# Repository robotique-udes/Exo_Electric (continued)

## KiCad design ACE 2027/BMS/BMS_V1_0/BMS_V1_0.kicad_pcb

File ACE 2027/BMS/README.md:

# BMS — Battery Management System

> Carte de gestion, de protection et de distribution de l'alimentation de l'exosquelette.

Le BMS est responsable de la gestion, de la protection et de la distribution de l'énergie du système. Il supervise les deux batteries, gère les séquences de commutation, protège les circuits contre les défauts et alimente les sous-systèmes critiques, notamment les rails **5 V** et **48 V**.

## Vue d'ensemble

Le BMS doit notamment :

- gérer l'arrêt d'urgence de l'exosquelette ;
- protéger chaque batterie individuellement ;
- sélectionner automatiquement ou manuellement la source d'alimentation active ;
- distribuer les tensions **5 V** et **48 V** aux sous-systèmes ;
- communiquer l'état du système au module principal (**MoBo**) ;
- sécuriser les circuits vis-à-vis des courts-circuits, de la polarité inversée et des surintensités.

## Objectifs fonctionnels

- gérer l'arrêt d'urgence de l'exosquelette ;
- intégrer des fusibles de sécurité : un par batterie, un par jambe et un pour le circuit 5 V ;
- inclure une protection contre la polarité inversée (back-EMF / courant inverse) ;
- mettre en place une stratégie de handshake ou équivalent pour éviter le court-circuit entre les batteries ;
- ajouter des LED indiquant l'état d'alimentation après les fusibles pour vérifier rapidement leur état ;
- gérer un courant continu de **4 A à 48 V** ;
- fournir **2,5 A à 5 V continu** pour les sous-systèmes (BIMU, MoBo et alimentation du BMS) ;
- fournir un indicateur de pourcentage de batterie restante ;
- intégrer une connexion de batterie de type **XT ?** ;
- prévoir une connexion Ethernet pour la distribution 5 V et le bus CAN ;
- intégrer une connexion **XT30** par jambe ;
- permettre le basculement automatique entre les batteries ;
- inclure des indicateurs visuels d'état autour des batteries.

# Conception

- Seuls les ESP32 du **MoBo** et du **BMS** disposent d'une connectivité sans fil. Les deux sont inclus dans le budget de puissance, mais seul le module sans fil du MoBo sera utilisé en fonctionnement normal.
- La consommation **MISC** correspond à une estimation des pertes du PCB, des pertes de conversion, des composants annexes et des LED.
- **LED_BMS** représente la puissance disponible pour des LED décoratives ou d'usage non critique. Elle ne fait pas partie du total de puissance de base et pourra être calculée une fois les besoins principaux fixés.

### Budget de puissance 5 V

Les estimations ci-dessous supposent un rail **3,3 V** et une marge de conversion de **20 %**.

| Charge | Hypothèse | Puissance estimée |
| --- | --- | ---: |
| MoBo | `(300 mA + 100 mA MISC) × 3,3 V` | **1,32 W** |
| BIMU | `(35 mA + 100 mA MISC) × 3,3 V x 5` | **2,25 W** |
| BMS | `(300 mA + 100 mA MISC) × 3,3 V` | **1,32 W** + `LED_BMS` |

Un rendement de **80 %** est retenu pour le convertisseur principal vers **5 V**. Cette hypothèse est volontairement prudente, car la tension de batterie peut varier significativement et le convertisseur doit couvrir une large plage d'entrée.

### Estimation des besoins du circuit 5 V

```text
P nécessaire = (1,32 W + 2,25 W + 1,32 W) / 0,80
            = 6,12 W

I sous 5 V = 6,12 W / 5 V
           = 1,224 A
```

Un convertisseur **5 V / 1.5 A** couvrirait donc l'estimation actuelle. Cependant, le câble Ethernet envisagé, avec des conducteurs **23 AWG**, est généralement estimé à environ **0,7 A par conducteur**. Avec trois conducteurs 5 V et trois conducteurs GND, la capacité théorique atteint :

```text
0,7 A × 3 = 2,1 A
```

Par prudence et pour garder une marge d'évolution, le convertisseur cible sera choisi dans une plage de **2 à 4 A**, selon les besoins confirmés et les composants disponibles. Un fusible de **2 A** en amont du câble est envisagé.

### Estimation des pertes de la diode de contrôle

Le courant traversant la diode est estimé dans le pire cas : **4 A sous 5 V**.

```text
I diode = 4 A × 5 V / 0,8 / 60
        = 0,42 A
```

En appliquant la formule donnée dans la documentation :

```text
P = 0,54 × IF + 0,08 × IF^2
P = 0,54 × 0,42 A + 0,08 × (0,42 A)^2
P = 0,24 W
```

Cette valeur correspond au pire cas et semble acceptable à ce stade. La température de fonctionnement devra toutefois être vérifiée avec le boîtier et le PCB définitifs.

---

## Sécurité et protection des fusibles

### Estimation du courant requis pour le rail 48 V

Le système est composé de :

- 4 moteurs, chacun consommant jusqu'à **0,8 A sous 48 V** ;
- une charge auxiliaire (contrôle) de **1 A sous 5 V**.

#### Courant nominal des moteurs

```text
I moteurs = 4 × 0,8 A
          = 3,2 A
```

#### Courant équivalent de la charge 5 V

En considérant un rendement du convertisseur de **80 %** :

```text
I 5V = (0,8 × 48 V) / (5 V × 1 A)
     = 0,13 A
```

#### Courant total

```text
I total = 3,2 A + 0,13 A
        = 3,33 A
```

#### Marge de sécurité

Avec une marge de sécurité de **25 %** :

```text
I fusible = 3,33 A × 1,25
          ≈ 4,17 A
```

Un fusible de **4 A** serait une valeur limite. Il serait judicieux d'envisager un fusible de **5 A** pour conserver une marge de fonctionnement plus confortable.

### Courant de démarrage

Le fusible doit supporter les pointes de courant produites lors du démarrage des moteurs sans ouvrir prématurément.

Le courant réel pendant le démarrage est :

```text
I start = I normal + I spike
```

Pour un courant de démarrage approximativement constant :

```text
I²t = I start² × t start
```

Une marge de sécurité peut ensuite être appliquée :

```text
I²t requis = I²t × M
```

où **M** représente la marge de sécurité.

### Calcul de la valeur de fusible pour un type slow blow

Pour calculer la valeur de fusible adaptée à une protection de type **slow blow**, il faut utiliser la formule suivante :

```text
I²t = I peak² × t pulse
```

et déterminer la valeur requise pour la fusible en fonction du profil de courant.

Un exemple de référence compatible avec ce type de besoins est disponible ici :

https://www.littelfuse.com/products/fuses-overcurrent-protection/fuses/axial-radial-thru-hole-fuses#Zi1zZXJpZXM9MzcyJm5mLW1heGltdW1fYWNfdm9sdGFnZV92X2RlY2ltYWw9NzAuLi4xMDAwJm5mLW5vbWluYWxfbWVsdGluZ19pX3NxdWFyZWRfdF9hX3NxdWFyZWRfcGVyX3NlY29uZF9kZWNpbWFsPTE2Li4uMzImY3E9KCU0MGxldmVsdGhyZWVjYXRlZ29yeSUzRCUzRCUyMkF4aWFsJTIwUmFkaWFsJTIwVGhydSUyMEhvbGUlMjBGdXNlcyUyMiklMjAoJTQwbGV2ZWxudW1iZXIlM0QlM0Q3KSUyMCglNDBsZXZlbHR3b2NhdGVnb3J5JTNEJTNEJTIyRnVzZXMlMjIpJTIwKCU0MGxldmVsb25lY2F0ZWdvcnklM0QlM0QlMjJGdXNlcyUyMCUyNiUyME92ZXJjdXJyZW50JTIwUHJvdGVjdGlvbiUyMik=

Mini fuse verre
https://www.digikey.ca/en/products/detail/littelfuse-inc/0225002-MXP/777781

https://www.digikey.ca/en/products/filter/fuses/139?s=N4IgjCBcoGwJxVAYygMwIYBsDOBTANCAPZQDaIAzHAKw0UgC6hADgC5QgDKrATgJYA7AOYgAvoTBwAHAmggUkDDgLEyIAAyNxIAExgALPsQg2HAKoC%2BrAPKoAsrnTYArj1whCzjgDUPIALaCHPpSfv7oAB4cBpraALQ6xgq8ziokkOTUWtqJGSCoznhaQA

## Choix mosfet
La priorité est de minimisé le RDS on pour limité les pertes durant l'utilisation. Il faut aussi gardé 20V de marge sur l'utilisation. Pour finir il faut gardé un Gate charge raisonnable pour limité le temps de transition des mosfet:

Premier choix 80V(31mO, 45nC)
https://www.digikey.ca/en/products/detail/vishay-siliconix/SQS181ELNW-T1-GE3/20512189

Deuxième choix 80V(17mO, 93nC)
https://www.digikey.ca/en/products/detail/mcc-micro-commercial-components/MCAC017P08Y-TP/25965041

Premier choix 100V(30mO, 68nC)
https://www.digikey.ca/en/products/detail/vishay-siliconix/SQJ211ELP-T1-GE3/13540573

Deuxième choix 100V(31mO, 73nC)
https://www.digikey.ca/en/products/detail/goford-semiconductor/GT250P10T/19524544

## calcul led 

Consommation maximum de 11W/m pour les bandes LEDS https://www.amazon.ca/BTF-LIGHTING-Similar-Individually-Addressable-Lighting/dp/B0F62XVXNS/ref=ast_sto_dp_puis?th=1
Donc on parle de 1.1W/m ou 0.22A

Mais une consommation normal serait plus 30% à 40% voir moins(le but est de les voir, mais sans plus), donc on parle de 0.44W/m ou 0.088A. 
---

## Points à confirmer avant validation finale

- référence exacte des batteries, tension minimale et tension maximale ;
- type de connecteur batterie (**XT ?**) et courant admissible réel ;
- courant de démarrage et courant continu de chaque jambe ;
- méthode de mesure de l'état de charge et précision attendue ;   comptage de columbs
- protocole de handshake pour la sélection de batterie et comportement en cas de défaut ;  Utilisation de 3 lectures de tensions
- validation thermique du convertisseur 5 V, des MOSFET et des fusibles ;  Probablement Négligeable

Faire circuit led pour support batterie

## Résumé

Le BMS est un élément central du système d'alimentation. Il doit offrir une protection robuste, une gestion fiable de la source d'énergie, un basculement entre batteries sans court-circuit, ainsi qu'une alimentation stable de la logique de contrôle et des sous-systèmes. Les estimations actuelles indiquent que le rail 5 V doit être dimensionné pour un convertisseur de l'ordre de **2 à 4 A**, tandis que la protection du rail 48 V doit être étudiée avec une marge suffisante pour supporter les pointes de démarrage des moteurs.

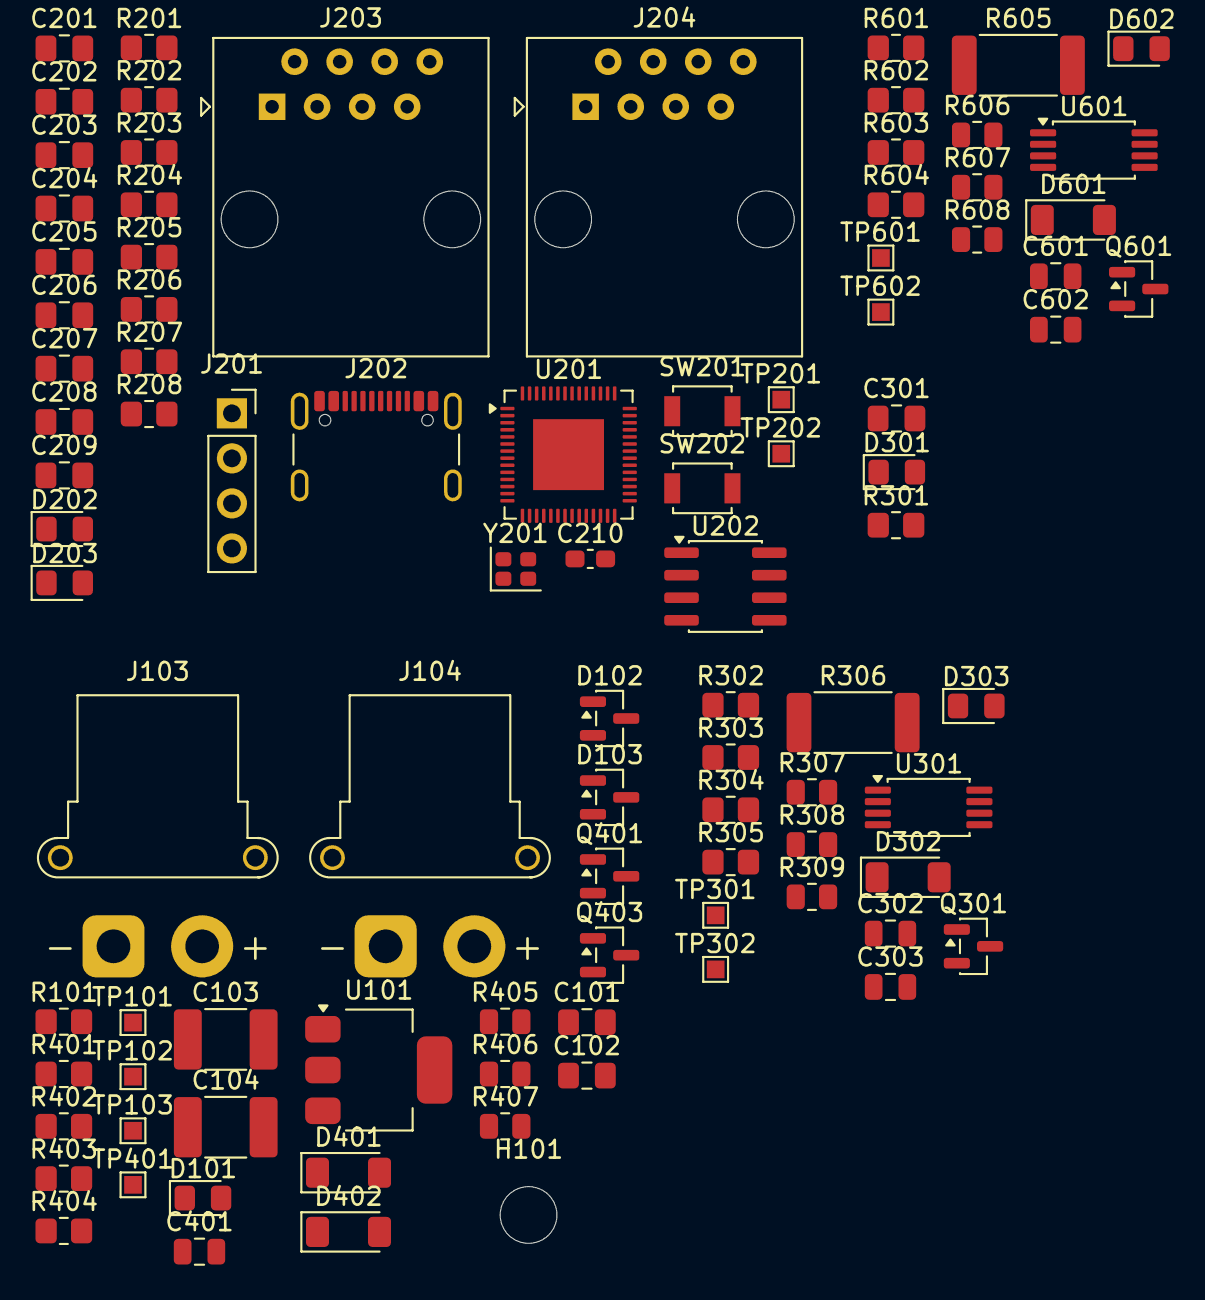
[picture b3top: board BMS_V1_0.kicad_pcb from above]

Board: 4 copper layers, 94 parts (0 on the bottom side), 41 nets, no tracks yet.

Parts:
C101, C102, C301: 4,7µF; C_0805_2012Metric_Pad1.18x1.45mm_HandSolder
C103, C104: 1nF; C_1812_4532Metric_Pad1.57x3.40mm_HandSolder
C201, C209: 22μF; C_0805_2012Metric_Pad1.18x1.45mm_HandSolder
C202, C203, C204, C205, C208: 0.1μF; C_0805_2012Metric_Pad1.18x1.45mm_HandSolder
C206, C207: 12pF; C_0805_2012Metric_Pad1.18x1.45mm_HandSolder
C210: 47nF; C_0603_1608Metric_Pad1.08x0.95mm_HandSolder
C302, C601: 0,1µF; C_0805_2012Metric
C303, C401, C602: 0.1uF; C_0805_2012Metric
D101, D301, D303, D602: POWER LED; LED_0805_2012Metric_Pad1.15x1.40mm_HandSolder
D102, D103: BAV99; SOT-23
D202: CONNECTED LED; LED_0805_2012Metric_Pad1.15x1.40mm_HandSolder
D203: ERROR LED; LED_0805_2012Metric_Pad1.15x1.40mm_HandSolder
D302, D401, D402, D601: BZV55B15; D_MiniMELF
H101: MountingHole; MountingHole_3.2mm_M3_ISO14580
J103: Jambe_gauche; AMASS_XT30PW-F_1x02_P2.50mm_Horizontal
J104: Jambe_droite; AMASS_XT30PW-F_1x02_P2.50mm_Horizontal
J201: UART_connector; PinSocket_1x04_P2.54mm_Vertical
J202: USB_C_Receptacle_USB2.0_16P; USB_C_Receptacle_GCT_USB4105-xx-A_16P_TopMnt_Horizontal
J203: MoBo; RJ45_Amphenol_54602-x08_Horizontal
J204: BIMU; RJ45_Amphenol_54602-x08_Horizontal
Q301, Q401, Q403, Q601: NTR2101P; SOT-23
R101, R205, R206, R301: 330Ω; R_0805_2012Metric_Pad1.20x1.40mm_HandSolder
R201, R202, R203, R204: 5.1KΩ; R_0805_2012Metric_Pad1.20x1.40mm_HandSolder
R207, R208: 50Ω; R_0805_2012Metric_Pad1.20x1.40mm_HandSolder
R302, R303, R304, R305, R401, R402, R403, R404, R601, R602, R603, R604: ???Ω; R_0805_2012Metric_Pad1.20x1.40mm_HandSolder
R306, R605: ???Ω; R_2512_6332Metric_Pad1.40x3.35mm_HandSolder
R307, R405, R606: ???; R_0805_2012Metric
R308, R406, R607: ???Ω; R_0805_2012Metric
R309, R407, R608: 100Ω; R_0805_2012Metric
SW201, SW202: SW_Push; SW_SPST_B3U-1000P
TP101: TP_GND_IN; TestPoint_Pad_1.0x1.0mm
TP102: TP_5V; TestPoint_Pad_1.0x1.0mm
TP103: TP_3v3; TestPoint_Pad_1.0x1.0mm
TP201: TP_CAN_P; TestPoint_Pad_1.0x1.0mm
TP202: TP_CAN_N; TestPoint_Pad_1.0x1.0mm
TP301, TP601: TP_Current; TestPoint_Pad_1.0x1.0mm
TP302, TP401, TP602: TP_Voltage; TestPoint_Pad_1.0x1.0mm
U101: AP7361C-33E; SOT-223-3_TabPin2
U201: ESP32-S3; QFN-56-1EP_7x7mm_P0.4mm_EP4x4mm
U202: SN65HVD232DR; SOIC-8_3.9x4.9mm_P1.27mm
U301, U601: INA240A2PW; TSSOP-8_4.4x3mm_P0.65mm
Y201: ABM8-40.000MHZ-10-D1G-T; Crystal_SMD_2016-4Pin_2.0x1.6mm

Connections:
+3.3V: C102.2, C103.1, C104.1, C201.1, C202.1, C208.1, C209.1, C302.1, C601.1, D102.2 (A), D103.2 (A), R101.1, R203.2, R204.2, TP103.1 (1_1), U101.3 (VO), U201.2 (VDD3P3), U201.3 (VDD3P3), U202.3 (VCC), U301.5 (V+), U301.6 (REF2), U601.5 (V+), U601.6 (REF2)
+5V: C101.2, C203.1, J201.4, J202.A4 (VBUS), J202.A9 (VBUS), J202.B4 (VBUS), J202.B9 (VBUS), J203.5, J203.6, J203.7, J204.7, TP102.1 (1_1), U101.1 (VI)
/Alimentation/Battery_Out_Droite: Q403.2 (S), R403.2, R605.2, R606.2, U601.3 (-)
/Alimentation/Battery_Out_Gauche: Q401.2 (S), R306.2, R307.2, R401.2, U301.3 (-)
/Alimentation/Battery_Sub_Circuit_Droite/Battery_P: Q601.2 (S), R601.2
/Alimentation/Battery_Sub_Circuit_Gauche/Battery_P: Q301.2 (S), R302.2
BOOT: C205.1, R203.1, SW202.2
CAN_N: D103.3 (K), J203.2, J204.2, R208.2, TP202.1 (1_1), U202.6 (CANL)
CAN_P: D102.3 (K), J203.1, J204.1, R207.1, TP201.1 (1_1), U202.7 (CANH)
Current_Sense_Droite: TP601.1 (1_1), U601.8
Current_Sense_Gauche: TP301.1 (1_1), U301.8
EN: C204.1, R204.1, SW201.2
GND: C101.1, C102.1, C103.2, C104.2, C201.2, C202.2, C203.2, C204.2, C205.2, C206.2, C207.2, C208.2, C209.2, C210.1, C302.2, C303.2, C401.2, C601.2, C602.2, D101.1 (K), D102.1 (K), D103.1 (K), D202.1 (K), D203.1 (K), D303.1 (K), D602.1 (K), J103.1, J104.1, J201.1, J202.A1 (GND), J202.A12 (GND), J202.B1 (GND), J202.B12 (GND), J203.3, J203.4, J203.8, J204.8, R201.2, R202.2, R303.1, R308.1, R402.1, R404.1, R406.1, R602.1, R607.1, SW201.1, SW202.1, TP101.1 (1_1), U101.2 (GND), U201.57 (GND), U202.2 (GND), U301.1 (GND), U301.4 (GND), U301.7 (REF1), U601.1 (GND), U601.4 (GND), U601.7 (REF1), Y201.2, Y201.4
unnamed: C210.2, R207.2, R208.1
unnamed: D101.2 (A), R101.2
unnamed: J202.A7 (D-), J202.B7 (D-)
unnamed: J202.A6 (D+), J202.B6 (D+)
unnamed: D202.2 (A), R205.1
unnamed: D203.2 (A), R206.1
unnamed: D302.2 (A), Q301.1 (G), R302.1
unnamed: D303.2 (A), R307.1, R308.2, R309.2
unnamed: D401.2 (A), Q401.1 (G), R401.1
unnamed: D402.2 (A), Q403.1 (G), R403.1
unnamed: D601.2 (A), Q601.1 (G), R601.1
unnamed: D602.2 (A), R606.1, R607.2, R608.2
unnamed: J202.A5 (CC1), R201.1
unnamed: J202.B5 (CC2), R202.1
unnamed: Q301.3 (D), R305.2, R306.1, U301.2 (+)
unnamed: R303.2, R304.2
unnamed: Q601.3 (D), R604.2, R605.1, U601.2 (+)
unnamed: R602.2, R603.2
unnamed: R405.1, R406.2, R407.2
unnamed: U201.55 (VDDA), U201.56 (VDDA)
Sortie_Selecteur: Q401.3 (D), Q403.3 (D), R405.2
U0RX: J201.2, U201.50 (U0RXD)
U0TX: J201.3, U201.49 (U0TXD)
Voltage_Sense_Droite: C602.1, R608.1, TP602.1 (1_1)
Voltage_Sense_Gauche: C303.1, R309.1, TP302.1 (1_1)
Voltage_Sense_Selecteur: C401.1, R407.1, TP401.1 (1_1)
XTAL_N: C207.1, U201.53 (XTAL_N), Y201.3
XTAL_P: C206.1, U201.54 (XTAL_P), Y201.1

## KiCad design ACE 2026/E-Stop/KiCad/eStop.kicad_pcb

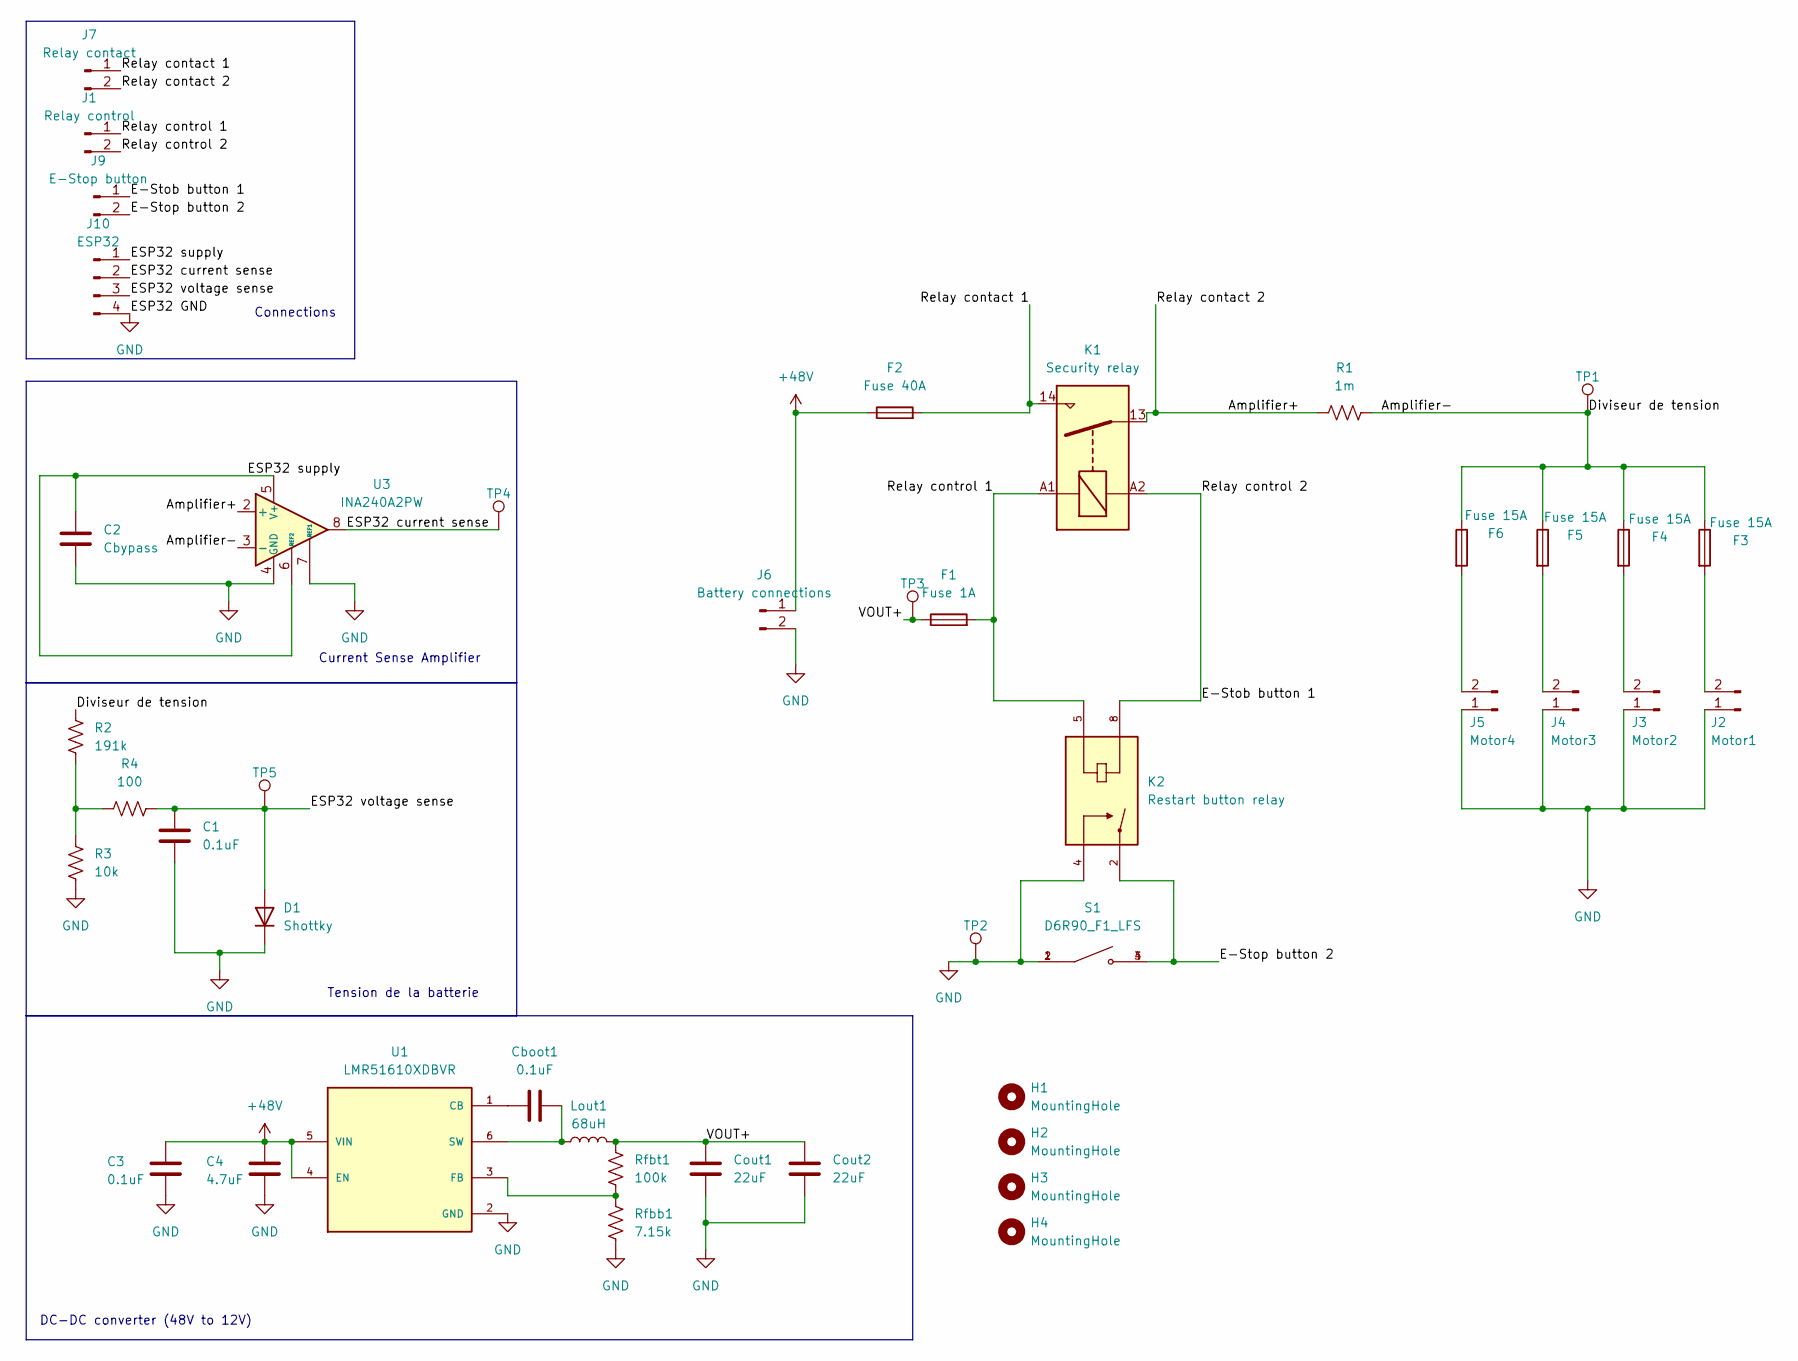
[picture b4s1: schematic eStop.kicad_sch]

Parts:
C1: 0.1uF; C_0805_2012Metric
C2: Cbypass; C_0805_2012Metric
C3: 0.1uF; C_1210_3225Metric_Pad1.33x2.70mm_HandSolder
C4: 4.7uF; C_2220_5750Metric_Pad1.97x5.40mm_HandSolder
Cboot1: 0.1uF; C_0805_2012Metric
Cout1, Cout2: 22uF; C_1210_3225Metric_Pad1.33x2.70mm_HandSolder
D1: Shottky; D_0603_1608Metric_Pad1.05x0.95mm_HandSolder
F1: Fuse 1A; 3557-15_KEY
F2: Fuse 40A; 40A fuse holder
F3, F4, F5, F6: Fuse 15A; 40A fuse holder
H1, H2, H3, H4: MountingHole; MountingHole_3.2mm_M3_DIN965
J1: Relay control; JST_EH_B2B-EH-A_1x02_P2.50mm_Vertical
J2: Motor1; AMASS_XT30U-F_1x02_P5.0mm_Vertical
J3: Motor2; AMASS_XT30U-F_1x02_P5.0mm_Vertical
J4: Motor3; AMASS_XT30U-F_1x02_P5.0mm_Vertical
J5: Motor4; AMASS_XT30U-F_1x02_P5.0mm_Vertical
J6: Battery connections; AMASS_XT60-M_1x02_P7.20mm_Vertical
J7: Relay contact; AMASS_XT60-M_1x02_P7.20mm_Vertical
J9: E-Stop button; JST_EH_B2B-EH-A_1x02_P2.50mm_Vertical
J10: ESP32; JST_EH_B4B-EH-A_1x04_P2.50mm_Vertical
K1: Security relay
K2: Restart button relay; RELAY_G6L-1P_DC12; Digi-Key_PN Z1229-ND
Lout1: 68uH; L_Bourns_SRR1260
R1: 1m; R_2512_6332Metric_Pad1.40x3.35mm_HandSolder
R2: 191k; R_0805_2012Metric
R3: 10k; R_0805_2012Metric
R4: 100; R_0805_2012Metric
Rfbb1: 7.15k; R_0805_2012Metric
Rfbt1: 100k; R_0805_2012Metric
S1: D6R90_F1_LFS; SW_D6R90_F1_LFS; PARTREV N/A
TP1, TP2, TP3, TP4, TP5: 1.0mm; TestPoint_Pad_D4.0mm
U1: LMR51610XDBVR; SOT95P280X145-6N; PARTREV B; DigiKey_Part_Number 296-LMR51610XDBVRCT-ND
U3: INA240A2PW; TSSOP-8_4.4x3mm_P0.65mm

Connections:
+48V: C3.1, C4.1, F2.1, J6.1, U1.4 (EN), U1.5 (VIN)
/Amplifier+: J7.2, K1.13, R1.1, U3.2 (+)
/Amplifier-: F3.1, F4.1, F5.1, F6.1, R1.2, R2.2, TP1.1, U3.3 (-)
/E-Stob button 1: J1.2, J9.1, K1.A2, K2.8; also elsewhere on the board
/E-Stop button 2: J9.2, K2.2, S1.3, S1.4; also elsewhere on the board
/ESP32 current sense: J10.2, TP4.1, U3.8; also elsewhere on the board
/ESP32 supply: C2.1, J10.1, U3.5 (V+), U3.6 (REF2); also elsewhere on the board
/ESP32 voltage sense: C1.1, D1.2 (A), J10.3, R4.1, TP5.1; also elsewhere on the board
/Relay contact 1: F2.2, J7.1, K1.14
/Relay control 1: F1.3, J1.1, K1.A1, K2.5; also elsewhere on the board
/VOUT+: Cout1.2, Cout2.2, F1.1, Lout1.2, Rfbt1.2, TP3.1
GND: C1.2, C2.2, C3.2, C4.2, Cout1.1, Cout2.1, D1.1 (K), J2.1, J3.1, J4.1, J5.1, J6.2, J10.4, K2.4, R3.1, Rfbb1.1, S1.1, S1.2, TP2.1, U1.2 (GND), U3.1 (GND), U3.4 (GND), U3.7 (REF1); also elsewhere on the board
unnamed: F3.2, J2.2
unnamed: F4.2, J3.2
unnamed: F5.2, J4.2
unnamed: F6.2, J5.2
unnamed: R2.1, R3.2, R4.2
unnamed: Cboot1.1, U1.1 (CB)
unnamed: Rfbb1.2, Rfbt1.1, U1.3 (FB)
unnamed: Cboot1.2, Lout1.1, U1.6 (SW)

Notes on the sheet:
Current Sense Amplifier
DC-DC converter (48V to 12V)
Tension de la batterie
Connections

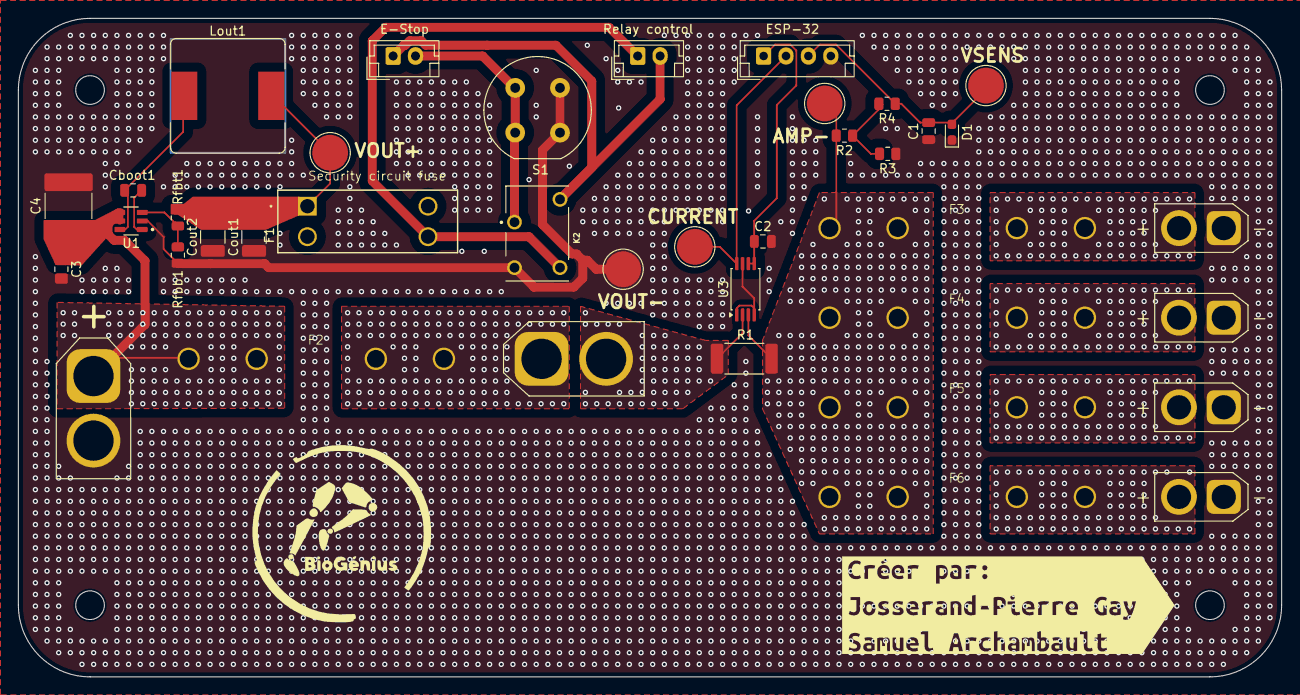
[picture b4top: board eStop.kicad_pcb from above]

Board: 2 copper layers, 141.0 x 73.5 mm, 44 parts (0 on the bottom side), 20 nets.

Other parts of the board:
E-Stop: E-Stop button; JST_EH_B2B-EH-A_1x02_P2.50mm_Vertical
ESP-32 : ESP32; JST_EH_B4B-EH-A_1x04_P2.50mm_Vertical
Relay control: Relay control; JST_EH_B2B-EH-A_1x02_P2.50mm_Vertical
kibuzzard-69BC9173: G***; kibuzzard-69BC9173

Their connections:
/E-Stob button 1: E-Stop.1, Relay control.2; also elsewhere on the board
/E-Stop button 2: E-Stop.2; also elsewhere on the board
/ESP32 current sense: ESP-32.2; also elsewhere on the board
/ESP32 supply: ESP-32.1; also elsewhere on the board
/ESP32 voltage sense: ESP-32.3; also elsewhere on the board
/Relay control 1: Relay control.1; also elsewhere on the board
GND: ESP-32.4; also elsewhere on the board

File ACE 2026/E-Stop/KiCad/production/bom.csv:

Designator,Footprint,Quantity,Value,LCSC Part #
"C1, C3, CBOOT1",0805,3,0.1uF,
C2,0805,1,Cbypass,
C4,2220,1,4.7uF,
"COUT1, COUT2",1210,2,22uF,
D1,0603,1,Shottky,
E-STOP,JST_EH_B2B-EH-A_1x02_P2.50mm_Vertical,1,E-Stop button,
ESP-32 ,JST_EH_B4B-EH-A_1x04_P2.50mm_Vertical,1,ESP32,
F1,3557-15_KEY,1,Fuse 1A,
F2,40A fuse holder,1,Fuse 40A,
"F3, F4, F5, F6",40A fuse holder,4,Fuse 15A,
J2,AMASS_XT30U-F_1x02_P5.0mm_Vertical,1,Motor1,
J3,AMASS_XT30U-F_1x02_P5.0mm_Vertical,1,Motor2,
J4,AMASS_XT30U-F_1x02_P5.0mm_Vertical,1,Motor3,
J5,AMASS_XT30U-F_1x02_P5.0mm_Vertical,1,Motor4,
J6,AMASS_XT60-M_1x02_P7.20mm_Vertical,1,Battery connections,
J7,AMASS_XT60-M_1x02_P7.20mm_Vertical,1,Relay contact,
K2,RELAY_G6L-1P_DC12,1,Restart button relay,
LOUT1,L_Bourns_SRR1260,1,68uH,
R1,2512,1,1m,
R2,0805,1,191k,
R3,0805,1,10k,
R4,0805,1,100,
RELAY CONTROL,JST_EH_B2B-EH-A_1x02_P2.50mm_Vertical,1,Relay control,
RFBB1,0805,1,7.15k,
RFBT1,0805,1,100k,
S1,SW_D6R90_F1_LFS,1,D6R90_F1_LFS,
"TP1, TP2, TP3, TP4, TP5",TestPoint_Pad_D4.0mm,5,1.0mm,
U1,SOT95P280X145-6N,1,LMR51610XDBVR,
U3,TSSOP-8_4.4x3mm_P0.65mm,1,INA240A2PW,

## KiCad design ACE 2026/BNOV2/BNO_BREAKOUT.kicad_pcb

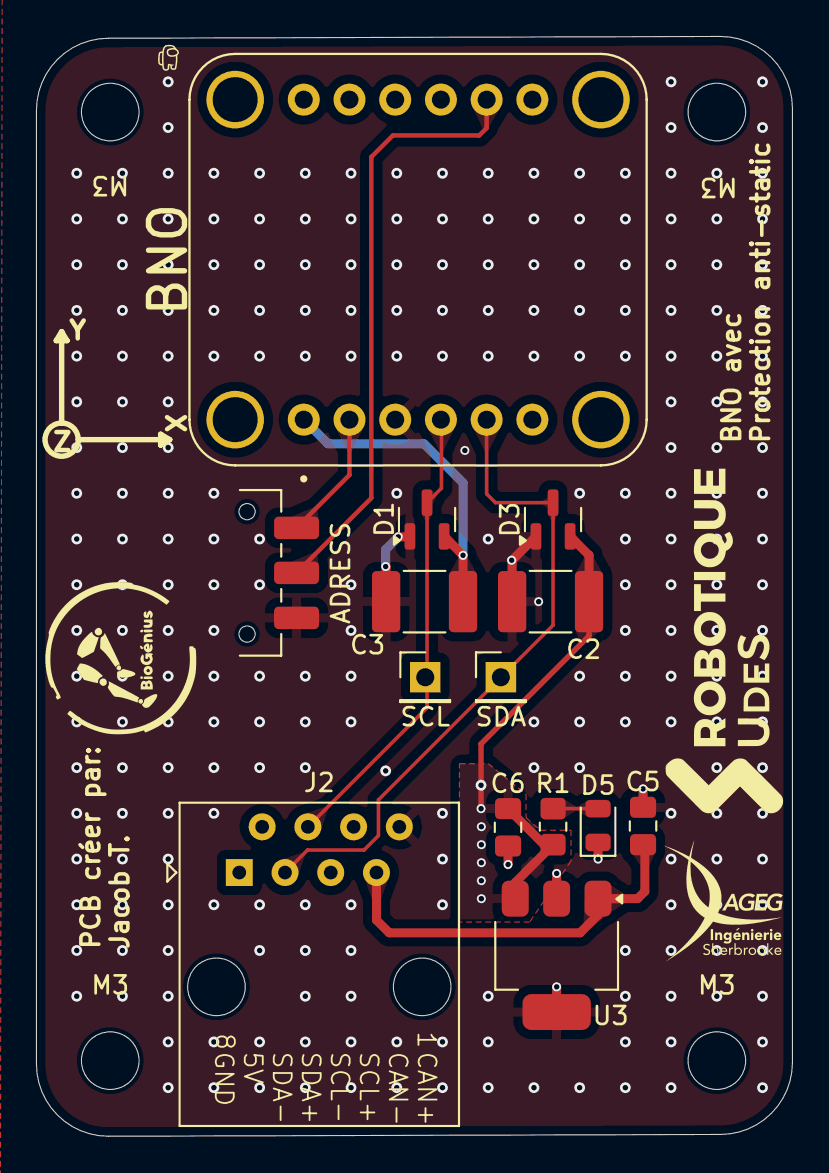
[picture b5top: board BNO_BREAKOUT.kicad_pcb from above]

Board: 2 copper layers, 42.0 x 61.1 mm, 16 parts (0 on the bottom side), 8 nets.

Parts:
ADRESS: SW_SPDT; SW_SPDT_CK_JS102011SAQN
BNO: 4754; MODULE_4754
C2, C3: 1n; C_1812_4532Metric_Pad1.57x3.40mm_HandSolder
C5, C6: 4,7µF; C_0805_2012Metric_Pad1.18x1.45mm_HandSolder
D1, D3: BAV99; SOT-23
D5: Green_power; D_0805_2012Metric
J2: RJ45; RJ45_Amphenol_54602-x08_Horizontal
M3, M3#2: MountingHole_3.2mm_M3
R1: 330; R_0805_2012Metric_Pad1.20x1.40mm_HandSolder
SCL: SCL; PinHeader_1x01_P2.54mm_Vertical
SDA: SDA; PinHeader_1x01_P2.54mm_Vertical
U3: AP7361C-33E; SOT-223-3_TabPin2

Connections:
/3V3: BNO.JP1_1 (VIN), C2.1, C3.1, C6.2, D1.2 (A), D3.2 (A), R1.1, U3.3 (VO)
/5V: C5.2, J2.7, U3.1 (VI)
/SCL: BNO.JP1_4 (SCL), D1.3 (K), J2.4, SCL.1
/SDA: BNO.JP1_5 (SDA), D3.3 (K), J2.3, SDA.1
GND: ADRESS.3 (C), BNO.JP1_3 (GND), C2.2, C3.2, C5.1, C6.1, D1.1 (K), D3.1 (K), D5.1 (K), J2.8, U3.2 (GND)
unnamed: D5.2 (A), R1.2
unnamed: ADRESS.1 (A), BNO.JP1_2 (3VO)
unnamed: ADRESS.2 (B), BNO.JP2_5 (DI)

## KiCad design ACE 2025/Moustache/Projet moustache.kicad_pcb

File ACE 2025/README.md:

# 2025 Standard électronique
Pour la fixation des pcb, il est standardisé d'utiliser des vis M3.
Ne pas utiliser de micro vias.
## PIN Layout pour la communication en cable ethernet
Pin 1: CAN+
Pin 2: CAN-
Pin 3: SCL+
Pin 4: SCL-
Pin 5: SDA+
Pin 6: SDA-
Pin 7: 5V
Pin 8: GND

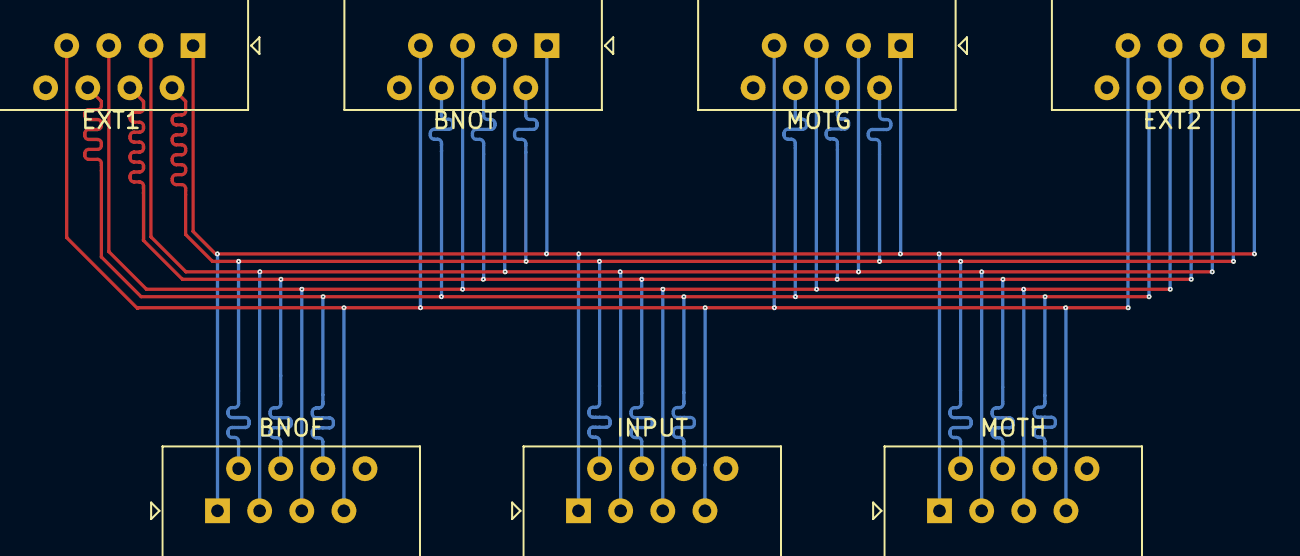
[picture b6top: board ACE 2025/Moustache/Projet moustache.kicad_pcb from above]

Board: 2 copper layers, 9 parts (0 on the bottom side), 8 nets.

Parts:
BNOF: RJ45; RJ45_Amphenol_54602-x08_Horizontal
BNOT: RJ45; RJ45_Amphenol_54602-x08_Horizontal
EXT1, EXT2: RJ45; RJ45_Amphenol_54602-x08_Horizontal
H1, H2: MountingHole; MountingHole_3.2mm_M3
INPUT: RJ45; RJ45_Amphenol_54602-x08_Horizontal
MOTG: RJ45; RJ45_Amphenol_54602-x08_Horizontal
MOTH: RJ45; RJ45_Amphenol_54602-x08_Horizontal

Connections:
+5V: BNOF.7, BNOT.7, EXT1.7, EXT2.7, INPUT.7, MOTG.7, MOTH.7
/CAN+: BNOF.1, BNOT.1, EXT1.1, EXT2.1, INPUT.1, MOTG.1, MOTH.1
/CAN-: BNOF.2, BNOT.2, EXT1.2, EXT2.2, INPUT.2, MOTG.2, MOTH.2
/SCL+: BNOF.3, BNOT.3, EXT1.3, EXT2.3, INPUT.3, MOTG.3, MOTH.3
/SCL-: BNOF.4, BNOT.4, EXT1.4, EXT2.4, INPUT.4, MOTG.4, MOTH.4
/SDA+: BNOF.5, BNOT.5, EXT1.5, EXT2.5, INPUT.5, MOTG.5, MOTH.5
/SDA-: BNOF.6, BNOT.6, EXT1.6, EXT2.6, INPUT.6, MOTG.6, MOTH.6
GND: BNOF.8, BNOT.8, EXT1.8, EXT2.8, INPUT.8, MOTG.8, MOTH.8

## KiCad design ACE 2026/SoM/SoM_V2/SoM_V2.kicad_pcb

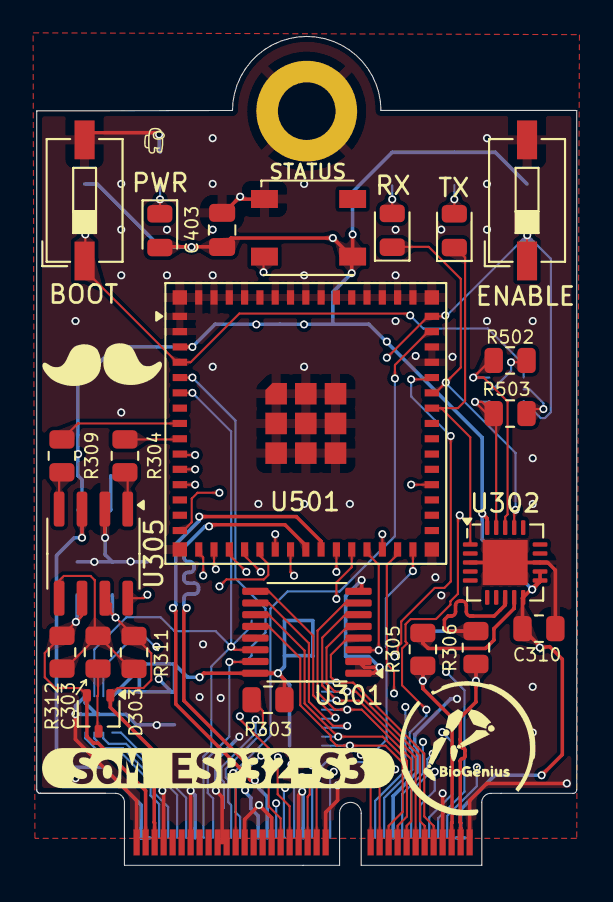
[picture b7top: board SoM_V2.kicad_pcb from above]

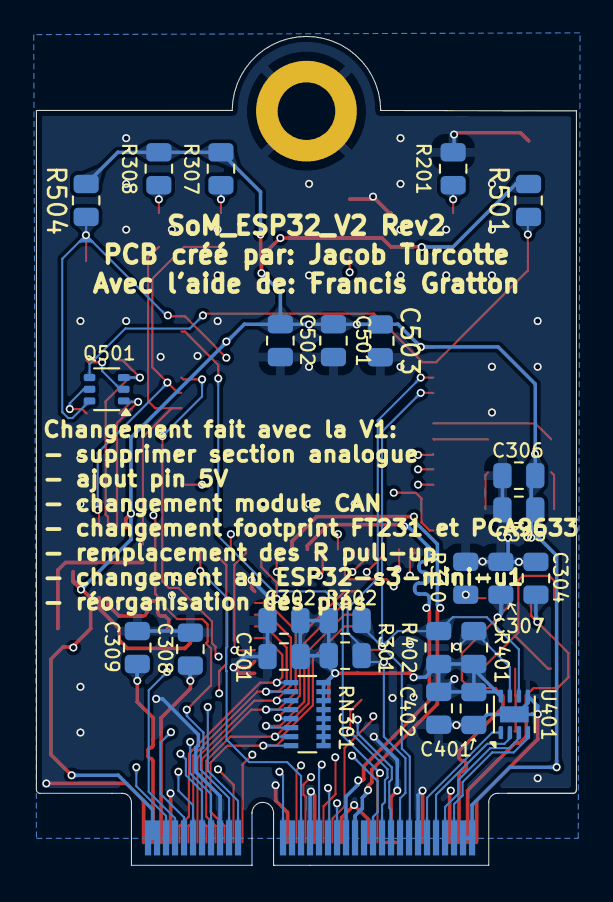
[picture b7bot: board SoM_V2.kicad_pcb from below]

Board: 4 copper layers, 30.0 x 46.1 mm, 51 parts (26 on the bottom side), 62 nets.

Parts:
BOOT: SW_BOOT; SW_DIP_SPSTx01_Slide_6.7x4.1mm_W6.73mm_P2.54mm_LowProfile_J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
C301, C501: 10µF; R_0805_2012Metric
C302, C304, C306, C307, C310, C502: 0.1µF; R_0805_2012Metric
C303, C305, C401, C503: 1µF; R_0805_2012Metric
C308, C309: 47pF; R_0805_2012Metric
C402: 100nF; R_0805_2012Metric
C403: 100n; C_0805_2012Metric
D303: SP0502BAJT; SOT-323_SC-70
ENABLE: SW_CHIP_EN; SW_DIP_SPSTx01_Slide_6.7x4.1mm_W6.73mm_P2.54mm_LowProfile_J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
PWR: GREEN; LED_0805_2012Metric
Q501: MBT3904DW1T1G; SOT-363_SC-70-6
R201, R307, R308: 330; R_0805_2012Metric
R301, R302, R303, R304, R309, R310, R401, R402: 1k; R_0805_2012Metric
R305, R306: 27; R_0805_2012Metric
R311, R312: 60; R_0805_2012Metric
R501, R502, R503, R504: 10k; R_0805_2012Metric
RN301: 1k; R_Array_Convex_8x0602
RX: TX; LED_0805_2012Metric
STATUS: FZ2812-5050; LED_Inolux_IN-PI554FCH_PLCC4_5.0x5.0mm_P3.2mm
TX: RX; LED_0805_2012Metric
U201: NGFF_E
U301: TCA9546APWR; TSSOP-16_4.4x5mm_P0.65mm
U302: FT231XQ; QFN-20-1EP_4x4mm_P0.5mm_EP2.5x2.5mm
U305: SN65HVD230; SOIC-8_3.9x4.9mm_P1.27mm
U401: PCA9633DP1; DFN-8-1EP_2x2mm_P0.5mm_EP0.9x1.6mm
U501: ESP32-S3-MINI-1U; ESP32-S2-MINI-1U
kibuzzard-66E094ED: G***; kibuzzard-66E094ED

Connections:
/Communication/CAN+: C307.2, D303.1 (K), R311.1, U201.71 (CAN_H_MCP2515), U305.7 (CANH)
/Communication/CAN-: C304.1, D303.2 (K), R312.2, U201.73 (CAN_L_MCP2515), U305.6 (CANL)
/Communication/D+: R306.2, U302.8 (USBDP)
/Communication/D-: R305.2, U302.9 (USBDM)
/Communication/DR+: C309.1, R306.1, U201.3 (USB_D+_FT231)
/Communication/DR-: C308.1, R305.1, U201.5 (USB_D-_FT231)
CHIP_EN: ENABLE.1, Q501.6 (C1), R504.1, U201.56 (RESET_ESP32), U501.45 (EN)
CS_1: U201.20 (CS_1), U501.15 (IO11)
CS_2: U201.21 (CS_2), U501.25 (IO21)
DEBUG+: U201.48 (USB_DEBUG_D+), U501.24 (IO20)
DEBUG-: U201.46 (USB_DEBUG_D-), U501.23 (IO19)
DTR: Q501.3 (C2), R502.1, U302.18 (~DTR)
GND: BOOT.2, C301.2, C302.2, C304.2, C305.2, C306.2, C307.1, C308.2, C309.2, C310.2, C401.2, C402.2, C403.2, C501.2, C502.2, C503.2, ENABLE.2, R201.2, R310.1, STATUS.1 (VSS), U201.1 (GND), U201.7 (GND), U201.18 (GND), U201.33 (GND), U201.38 (GND), U201.39 (GND), U201.45 (GND), U201.51 (GND), U201.55 (GND), U201.57 (GND), U201.62 (GND), U201.63 (GND), U201.69 (GND), U201.75 (GND), U301.1 (A0), U301.2 (A1), U301.8 (GND), U301.13 (A2), U302.3 (GND), U302.13 (GND), U302.21 (GND), U305.2 (GND), U401.5 (GND), U501.1 (GND), U501.2 (GND), U501.42 (GND), U501.43 (GND), U501.46 (GND), U501.47 (GND), U501.48 (GND), U501.49 (GND), U501.50 (GND), U501.51 (GND), U501.52 (GND), U501.53 (GND), U501.54 (GND), U501.55 (GND), U501.56 (GND), U501.57 (GND), U501.58 (GND), U501.59 (GND), U501.60 (GND), U501.61 (GND), U501.62 (GND), U501.63 (GND), U501.64 (GND), U501.65 (GND)
GPIO0_BOOT: BOOT.1, Q501.4 (E2), R501.1, U501.4 (IO0)
GPIO4/RXD: R309.1, U501.8 (IO4)
GPIO5/TXD: R304.1, U501.9 (IO5)
GPIO15: U201.40 (GPIO15), U501.19 (IO15)
GPIO16: U201.41 (GPIO16), U501.20 (IO16)
GPIO17_U1_TXD: U201.22 (UART_TX), U501.21 (IO17)
GPIO18_U1_RXD: U201.32 (UART_RX), U501.22 (IO18)
GPIO26: U201.42 (GPIO26), U501.26 (IO26)
GPIO33: U201.43 (GPIO33), U501.28 (IO33)
GPIO34: U201.44 (GPIO34), U501.29 (IO34)
GPIO38_ADDRESSABLE_LED: STATUS.2 (DIN), U201.6 (GPIO38&LED), U501.34 (IO38)
GPIO45: U201.52 (GPIO45), U501.41 (IO45)
GPIO46: U201.53 (GPIO46), U501.44 (IO46)
GPIO48/CAN_INT: U201.36 (GPIO48), U501.30 (IO48)
I2C_SCL_0_TCA: RN301.2 (R2.1), U201.11 (I2C_SCL_1_TCA), U301.5 (SC0)
I2C_SCL_1_TCA: RN301.4 (R4.1), U201.15 (I2C_SCL_2_TCA), U301.7 (SC1)
I2C_SCL_2_TCA: RN301.6 (R6.1), U201.16 (I2C_SCL_3_TCA), U301.10 (SC2)
I2C_SCL_3_TCA: RN301.8 (R8.1), U201.19 (I2C_SCL_4_TCA), U301.12 (SC3)
I2C_SCL_ESP32: R302.2, R402.2, U201.60 (I2C_SCL_ESP32), U301.14 (SCL), U401.6 (SCL6), U501.6 (IO2)
I2C_SDA_0_TCA: RN301.1 (R1.1), U201.9 (I2C_SDA_1_TCA), U301.4 (SD0)
I2C_SDA_1_TCA: RN301.3 (R3.1), U201.13 (I2C_SDA_2_TCA), U301.6 (SD1)
I2C_SDA_2_TCA: RN301.5 (R5.1), U201.14 (I2C_SDA_3_TCA), U301.9 (SD2)
I2C_SDA_3_TCA: RN301.7 (R7.1), U201.17 (I2C_SDA_4_TCA), U301.11 (SD3)
I2C_SDA_ESP32: R301.2, R401.2, U201.58 (I2C_SDA_ESP32), U301.15 (SDA), U401.7 (SDA), U501.5 (IO1)
I2S_BCLK: U201.8 (I2S_BCLK), U501.16 (IO12)
I2S_DIN/DOUT: U201.12 (I2S_DIN/DOUT), U501.18 (IO14)
I2S_WS: U201.10 (I2S_WS), U501.17 (IO13)
unnamed: PWR.1 (K), R201.1
unnamed: R307.1, RX.2 (A)
unnamed: R308.1, TX.2 (A)
unnamed: C303.2, D303.3 (A)
unnamed: Q501.2 (B1), R502.2
unnamed: Q501.5 (B2), R503.2
unnamed: U201.64 (PWM_1_PCA), U401.1 (PWM1)
unnamed: U201.66 (PWM_2_PCA), U401.2 (PWM2)
unnamed: U201.68 (PWM_3_PCA), U401.3 (PWM3)
unnamed: U201.70 (PWM_4_PCA), U401.4 (PWM4)
unnamed: R304.2, U305.1 (D)
unnamed: R309.2, U305.4 (R)
unnamed: R310.2, U305.8 (Rs)
RESET_OTHERS: R303.2, U201.54 (RESET_AUTRES), U301.3 (RESET_N), U501.27 (IO47)
RTS: Q501.1 (E1), R503.1, U302.19 (~RTS)
SPI_CLK_ESP32: U201.23 (SPI_CLK), U501.10 (IO6)
SPI_MISO_ESP32: U201.37 (SPI_MISO), U501.12 (IO8)
SPI_MOSI_ESP32: U201.35 (SPI_MOSI), U501.11 (IO7)
U0RXD: RX.1 (K), U302.17 (TXD), U501.40 (RXD0)
U0TXD: TX.1 (K), U302.1 (RXD), U501.39 (TXD0)
Vcc_3V3: C301.1, C302.1, C305.1, C306.1, C310.1, C401.1, C402.1, C403.1, C501.1, C502.1, C503.1, PWR.2 (A), R301.1, R302.1, R303.1, R307.2, R308.2, R401.1, R402.1, R501.2, R504.2, RN301.9 (R8.2), RN301.10 (R7.2), RN301.11 (R6.2), RN301.12 (R5.2), RN301.13 (R4.2), RN301.14 (R3.2), RN301.15 (R2.2), RN301.16 (R1.2), STATUS.3 (VDD), U201.2 (Vcc_3v3), U201.4 (Vcc_3v3), U201.72 (Vcc_3v3), U201.74 (Vcc_3v3), U301.16 (VCC), U302.10 (3V3OUT), U302.11 (~RESET), U302.12 (VCC), U302.20 (VCCIO), U305.3 (VCC), U401.8 (VCC), U501.3 (3V3)
Vref_CAN: C303.1, R311.2, R312.1, U305.5 (Vref)
